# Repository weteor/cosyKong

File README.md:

### cos(y) Kong

30 or 36 key 3row keyboards with col stagger

## Features

- single pcb with optional break off outer colums 
- Hotswap sockets (MX)
- onboard rp2040
- production files for pcba
- case files are supplied (stl, dxf, as well as cadquery files)
- QMK with vial support
- completely open source, permissive license ([CERN-OHL-P](https://cern-ohl.web.cern.ch/home))

## Want one?

All production files you need to build your own board can be found [here](./prod/).

The case has no bottom and ends right below the HS Sockets. You may either it as is, but preferably use some 2-3mm self-adhesive neopren on the whole pcb. The case may be hard to print on a FDM Printer, so maybe use a service to print it in resin. The cases on the picture are both made from white resin and were spraypainted.

It's advised to get the pcb's preassembled, since the MCU is really hard to solder per hand. Pick and place as well as BOM files can be found in the prod folder.

Apart from the pcb and optionally a case you need:
- 30-36 hotswap sockets
- 30-36 of your favourite switches

just solder the HS Socket, plug in your switches and you should be good to go.

### firmware
firmware configs for qmk and vial can be found in the [firmware folder].

The first time the pcb is plugged in, the bootloader will provide a drive to upload the firmware file. 

### the rest

Everything in this repository is free to use however you might see fit. If you want to support me and my projects, please consider linking back to this repository if you build/change/use anything.

If you would like to send me a tip, you could do it [here](https://ko-fi.com/weteor) (Please don't feel like you have to).

### more pictures

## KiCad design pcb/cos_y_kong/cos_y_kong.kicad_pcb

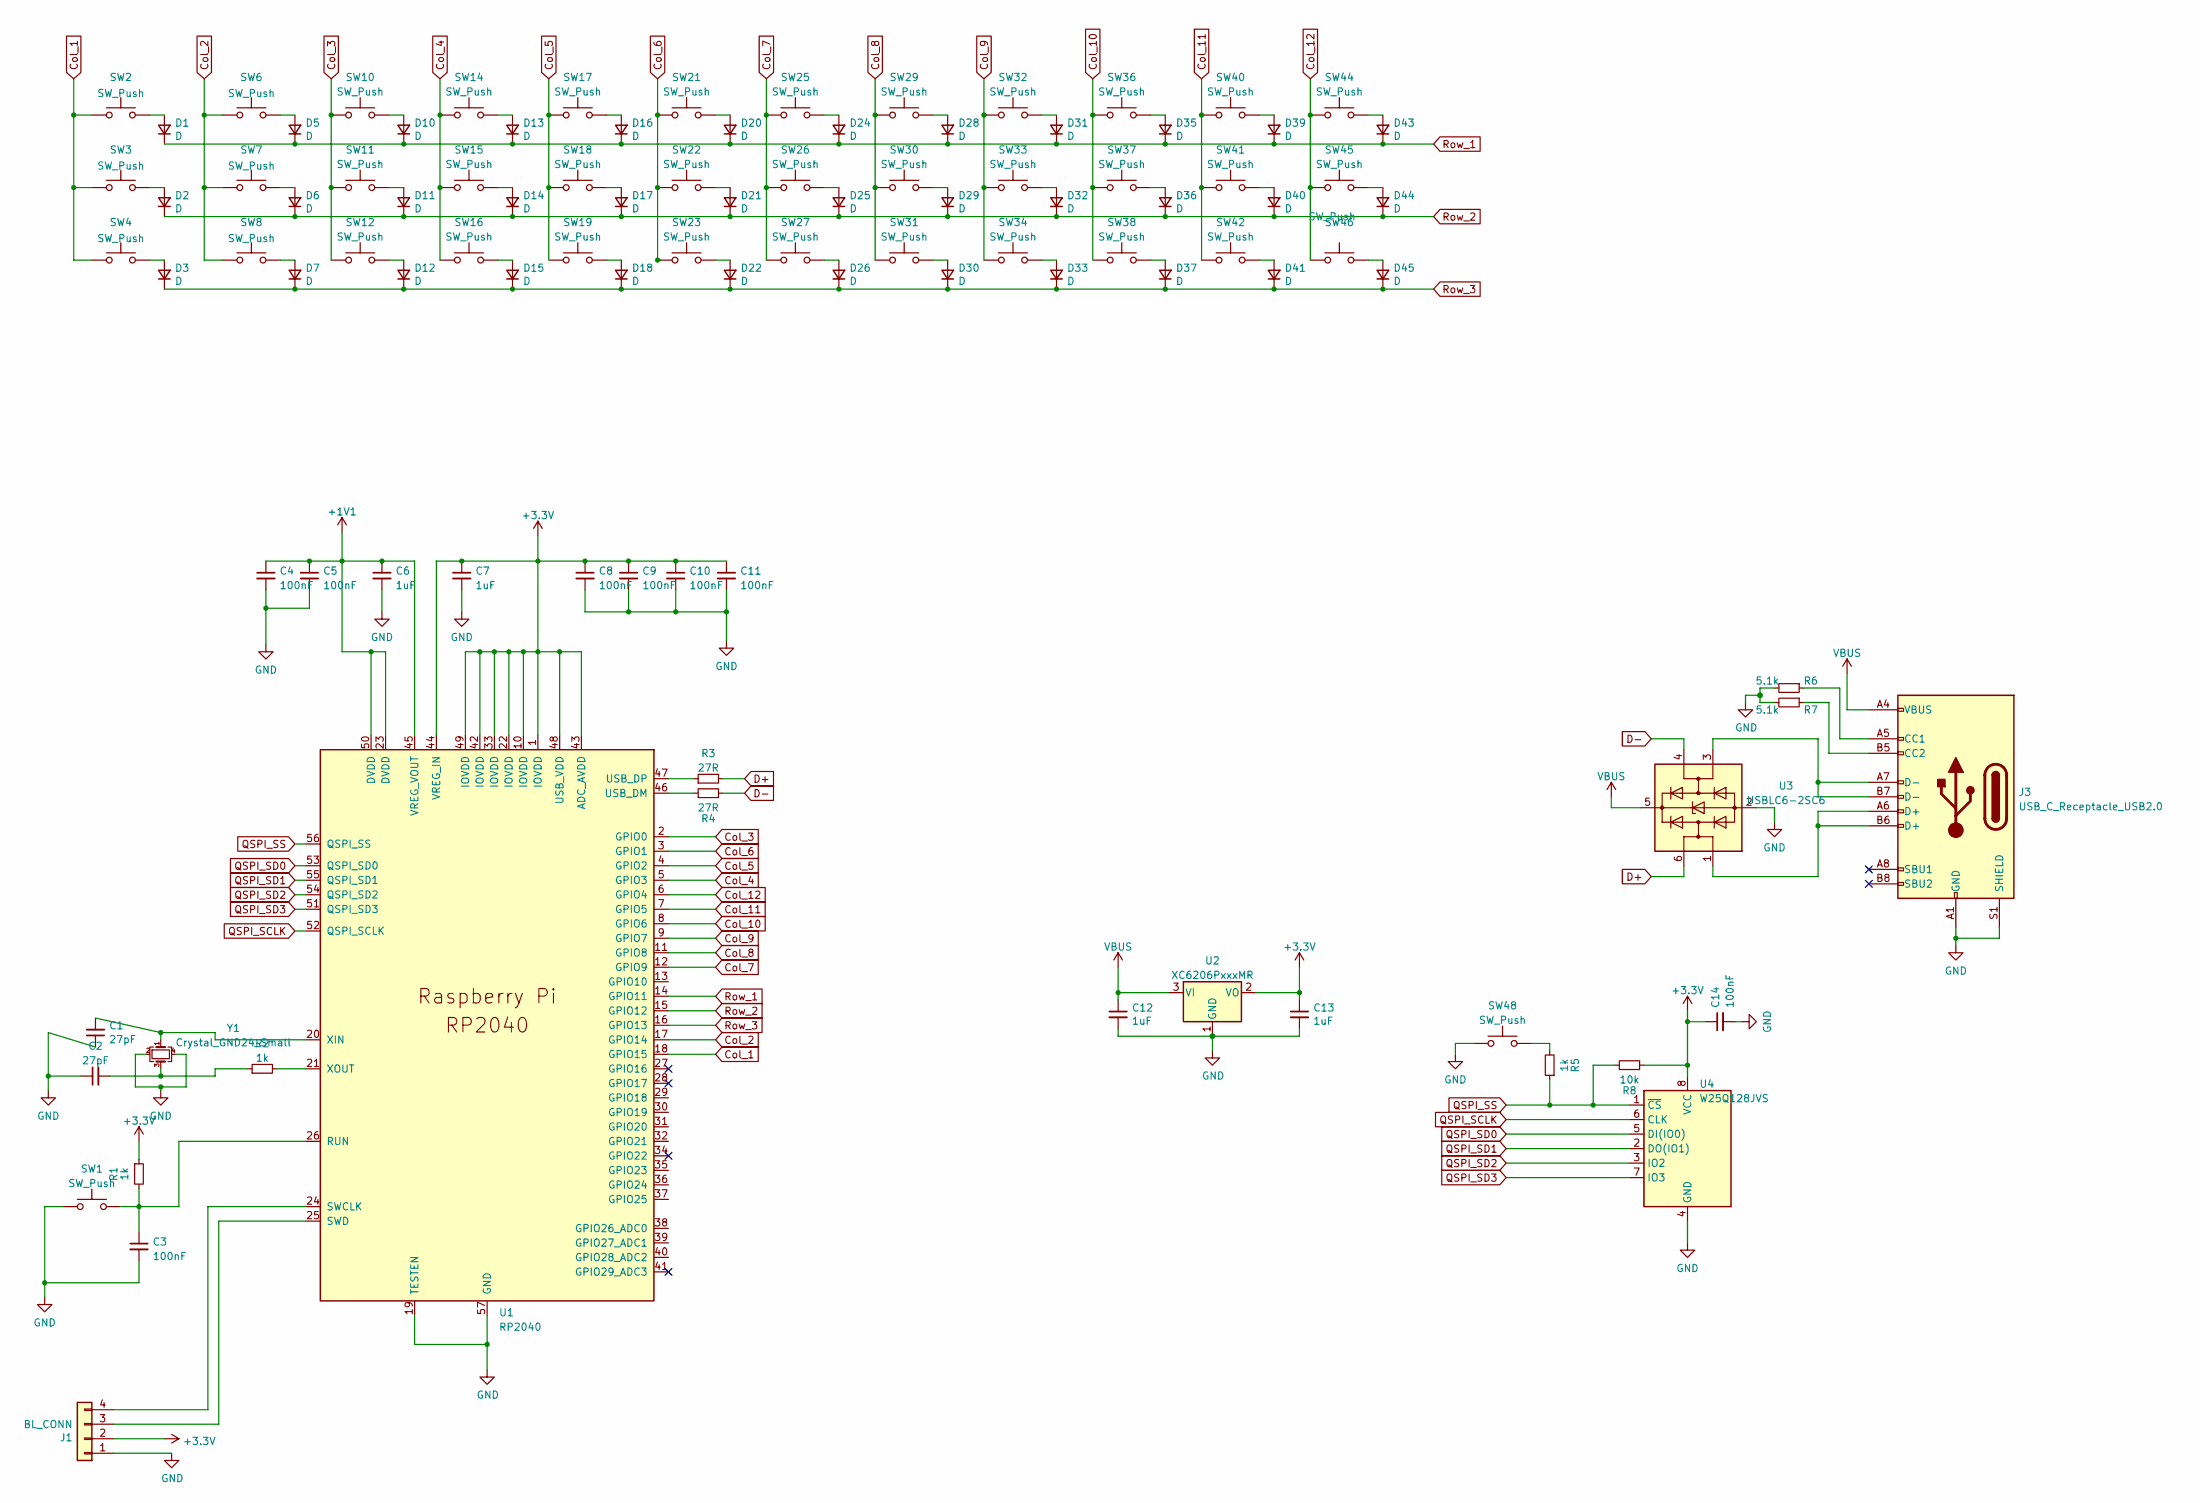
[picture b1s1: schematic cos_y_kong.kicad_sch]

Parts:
C1, C2: 27pF; C_0402_HandSolder
C3, C4, C5, C8, C9, C10, C11, C14: 100nF; C_0402_HandSolder
C6, C7, C12, C13: 1uF; C_0402_HandSolder
D1, D2, D3, D5, D6, D7, D10, D11, D12, D13, D14, D15, D16, D17, D18, D20, D21, D22, D24, D25, D26, D28, D29, D30, D31, D32, D33, D35, D36, D37, D39, D40, D41, D43, D44, D45: D; D_SOD-123
J1: BL_CONN; PinHeader_1x04_P2.54mm_Vertical
J3: USB_C_Receptacle_USB2.0; USB-C-12-Pin-MidMount
R1, R2, R5: 1k; R_0402_HandSolder
R3, R4: 27R; R_0402_HandSolder
R6, R7: 5.1k; R_0402_HandSolder
R8: 10k; R_0402_HandSolder
SW1, SW48: SW_Push; Micro_Push_Button_3x6x2.5mm
SW2, SW3, SW4, SW6, SW7, SW8, SW10, SW11, SW12, SW14, SW15, SW16, SW17, SW18, SW19, SW21, SW22, SW23, SW25, SW26, SW27, SW29, SW30, SW31, SW32, SW33, SW34, SW36, SW37, SW38, SW40, SW41, SW42, SW44, SW45, SW46: SW_Push; CherryMX_Hotswap
U1: RP2040; RP2040-QFN-56
U2: XC6206PxxxMR; SOT-23-3
U3: USBLC6-2SC6; SOT-23-6
U4: W25Q128JVS; SOIC-8_5.23x5.23mm_P1.27mm
Y1: Crystal_GND24_Small; Crystal_SMD_2520-4Pin_2.5x2.0mm

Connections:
+1V1: C4.1, C5.1, C6.1, U1.23 (DVDD), U1.45 (VREG_VOUT), U1.50 (DVDD)
+3.3V: C7.1, C8.1, C9.1, C10.1, C11.1, C13.1, C14.1, J1.2, R1.1, R8.2, U1.1 (IOVDD), U1.10 (IOVDD), U1.22 (IOVDD), U1.33 (IOVDD), U1.42 (IOVDD), U1.43 (ADC_AVDD), U1.44 (VREG_IN), U1.48 (USB_VDD), U1.49 (IOVDD), U2.2 (VO), U4.8 (VCC)
Col_1: SW2.1, SW3.1, SW4.1, U1.18 (GPIO15)
Col_2: SW6.1, SW7.1, SW8.1, U1.17 (GPIO14)
Col_3: SW10.1, SW11.1, SW12.1, U1.2 (GPIO0)
Col_4: SW14.1, SW15.1, SW16.1, U1.5 (GPIO3)
Col_5: SW17.1, SW18.1, SW19.1, U1.4 (GPIO2)
Col_6: SW21.1, SW22.1, SW23.1, U1.3 (GPIO1)
Col_7: SW25.1, SW26.1, SW27.1, U1.12 (GPIO9)
Col_8: SW29.1, SW30.1, SW31.1, U1.11 (GPIO8)
Col_9: SW32.1, SW33.1, SW34.1, U1.9 (GPIO7)
Col_10: SW36.1, SW37.1, SW38.1, U1.8 (GPIO6)
Col_11: SW40.1, SW41.1, SW42.1, U1.7 (GPIO5)
Col_12: SW44.1, SW45.1, SW46.1, U1.6 (GPIO4)
D+: R3.2, U3.6 (I/O1)
D-: R4.2, U3.4 (I/O2)
GND: C1.1, C2.1, C3.2, C4.2, C5.2, C6.2, C7.2, C8.2, C9.2, C10.2, C11.2, C12.2, C13.2, C14.2, J1.1, J3.A1 (GND), J3.A12 (GND), J3.B1 (GND), J3.B12 (GND), J3.S1 (SHIELD), R6.2, R7.2, SW1.1, SW48.1, U1.19 (TESTEN), U1.57 (GND), U2.1 (GND), U3.2 (GND), U4.4 (GND), Y1.2, Y1.4
unnamed: C2.2, R2.1, Y1.3
unnamed: D1.2 (A), SW2.2
unnamed: D2.2 (A), SW3.2
unnamed: D3.2 (A), SW4.2
unnamed: D5.2 (A), SW6.2
unnamed: D6.2 (A), SW7.2
unnamed: D7.2 (A), SW8.2
unnamed: D10.2 (A), SW10.2
unnamed: D11.2 (A), SW11.2
unnamed: D12.2 (A), SW12.2
unnamed: D13.2 (A), SW14.2
unnamed: D14.2 (A), SW15.2
unnamed: D15.2 (A), SW16.2
unnamed: D16.2 (A), SW17.2
unnamed: D17.2 (A), SW18.2
unnamed: D18.2 (A), SW19.2
unnamed: D20.2 (A), SW21.2
unnamed: D21.2 (A), SW22.2
unnamed: D22.2 (A), SW23.2
unnamed: D24.2 (A), SW25.2
unnamed: D25.2 (A), SW26.2
unnamed: D26.2 (A), SW27.2
unnamed: D28.2 (A), SW29.2
unnamed: D29.2 (A), SW30.2
unnamed: D30.2 (A), SW31.2
unnamed: D31.2 (A), SW32.2
unnamed: D32.2 (A), SW33.2
unnamed: D33.2 (A), SW34.2
unnamed: D35.2 (A), SW36.2
unnamed: D36.2 (A), SW37.2
unnamed: D37.2 (A), SW38.2
unnamed: D39.2 (A), SW40.2
unnamed: D40.2 (A), SW41.2
unnamed: D41.2 (A), SW42.2
unnamed: D43.2 (A), SW44.2
unnamed: D44.2 (A), SW45.2
unnamed: D45.2 (A), SW46.2
unnamed: J1.3, U1.25 (SWD)
unnamed: J1.4, U1.24 (SWCLK)
unnamed: J3.A5 (CC1), R6.1
unnamed: J3.B5 (CC2), R7.1
unnamed: J3.A6 (D+), J3.B6 (D+), U3.1 (I/O1)
unnamed: J3.A7 (D-), J3.B7 (D-), U3.3 (I/O2)
unnamed: R5.2, SW48.2
unnamed: C3.1, R1.2, SW1.2, U1.26 (RUN)
unnamed: R4.1, U1.46 (USB_DM)
unnamed: R3.1, U1.47 (USB_DP)
unnamed: C1.2, U1.20 (XIN), Y1.1
unnamed: R2.2, U1.21 (XOUT)
QSPI_SCLK: U1.52 (QSPI_SCLK), U4.6 (CLK)
QSPI_SD0: U1.53 (QSPI_SD0), U4.5 (DI(IO0))
QSPI_SD1: U1.55 (QSPI_SD1), U4.2 (DO(IO1))
QSPI_SD2: U1.54 (QSPI_SD2), U4.3 (IO2)
QSPI_SD3: U1.51 (QSPI_SD3), U4.7 (IO3)
QSPI_SS: R5.1, R8.1, U1.56 (QSPI_SS), U4.1 (~CS)
Row_1: D1.1 (K), D5.1 (K), D10.1 (K), D13.1 (K), D16.1 (K), D20.1 (K), D24.1 (K), D28.1 (K), D31.1 (K), D35.1 (K), D39.1 (K), D43.1 (K), U1.14 (GPIO11)
Row_2: D2.1 (K), D6.1 (K), D11.1 (K), D14.1 (K), D17.1 (K), D21.1 (K), D25.1 (K), D29.1 (K), D32.1 (K), D36.1 (K), D40.1 (K), D44.1 (K), U1.15 (GPIO12)
Row_3: D3.1 (K), D7.1 (K), D12.1 (K), D15.1 (K), D18.1 (K), D22.1 (K), D26.1 (K), D30.1 (K), D33.1 (K), D37.1 (K), D41.1 (K), D45.1 (K), U1.16 (GPIO13)
VBUS: C12.1, J3.A4 (VBUS), J3.A9 (VBUS), J3.B4 (VBUS), J3.B9 (VBUS), U2.3 (VI), U3.5 (VBUS)

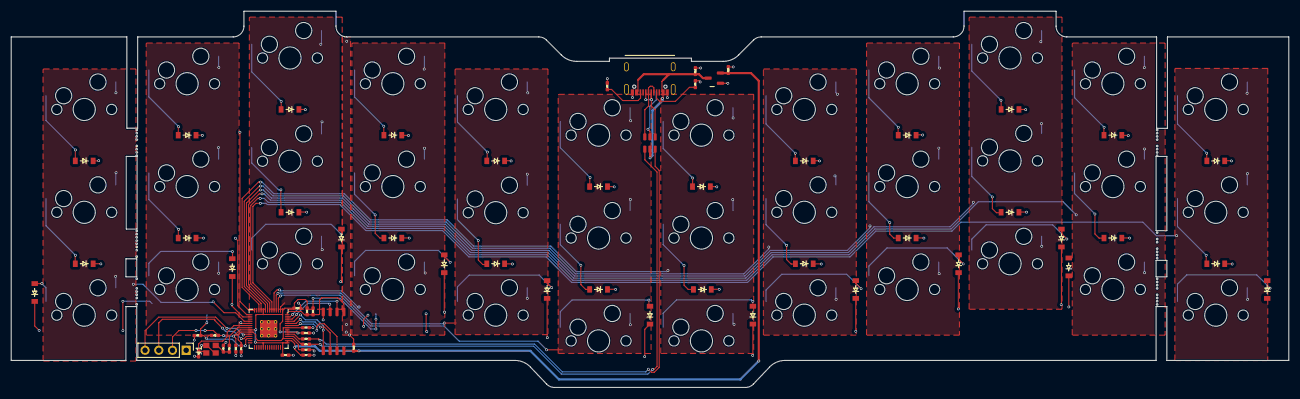
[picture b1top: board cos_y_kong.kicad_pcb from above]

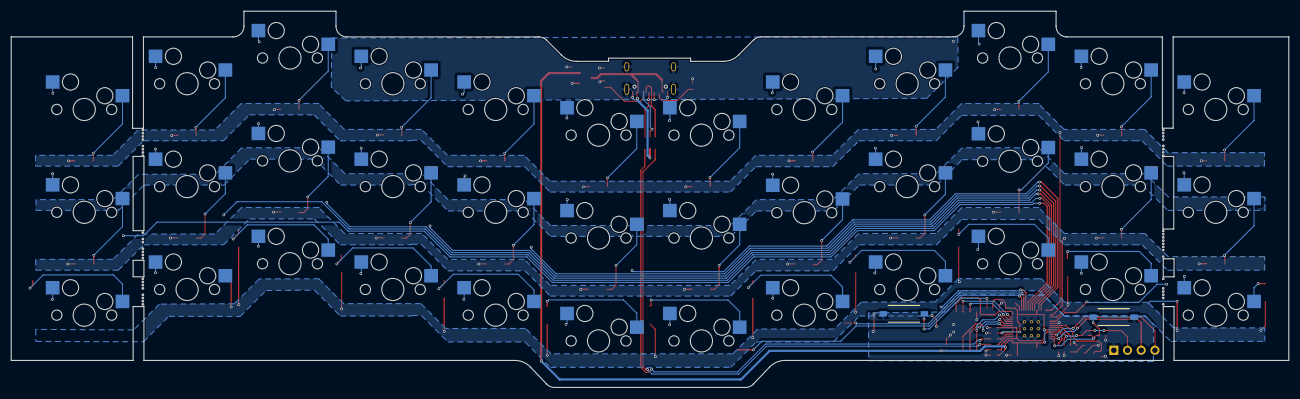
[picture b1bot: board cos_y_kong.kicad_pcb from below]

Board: 2 copper layers, 236.6 x 69.7 mm, 103 parts (2 on the bottom side), 76 nets.

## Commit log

2023-07-25 add pcb data
2023-07-25 add case data
2023-07-25 add production files pcb/case
2023-07-25 add readme and license
2023-07-25 add imgs
2023-07-25 add firmware
